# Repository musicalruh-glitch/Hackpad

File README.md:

### **Hackpad**

This hackpad is an extension of my regular keyboard! It makes it easier to game and change audio. The Hackpad is Bluetooth, so it'll connect to the PC. Unfortuneately.. I FORGOT TO ADD SOMETHING UNDERTALE RELATED GRAHHHH so the plan is when I get my CAD, I'll paint an undertale heart on the case or something
:DDD that's basically all there is to it lol, originally it was only 3 keys but I wanted to end off the design weeks with a bang, so here it is!! An extension of the keyboard, if all the arrow keys are separated, that makes it infinitely easier to game and stuff, volume buttons too because why not. Oh and the OLED screen because why not heheh. 

___

——

## **Here’s what each button does!**
Switches:
1. SW1: Same function as up arrow key on keyboard
2. SW2: Same function as down arrow key on keyboard
3. SW3: Same function as left arrow key on keyboard
4. SW4: Same function as right arrow key on keyboard
5. SW5: Same function as volume up key on keyboard
6. SW6: Same function as volume down key on keyboard
7. SW7: Same function as mute key on keyboard

There's also an OLED screen, it'll display whether the Hackpad is connected or not! It's findable as "Hackpad" when you turn bluetooth on. Seems a bit generic lol, I may want to change that.

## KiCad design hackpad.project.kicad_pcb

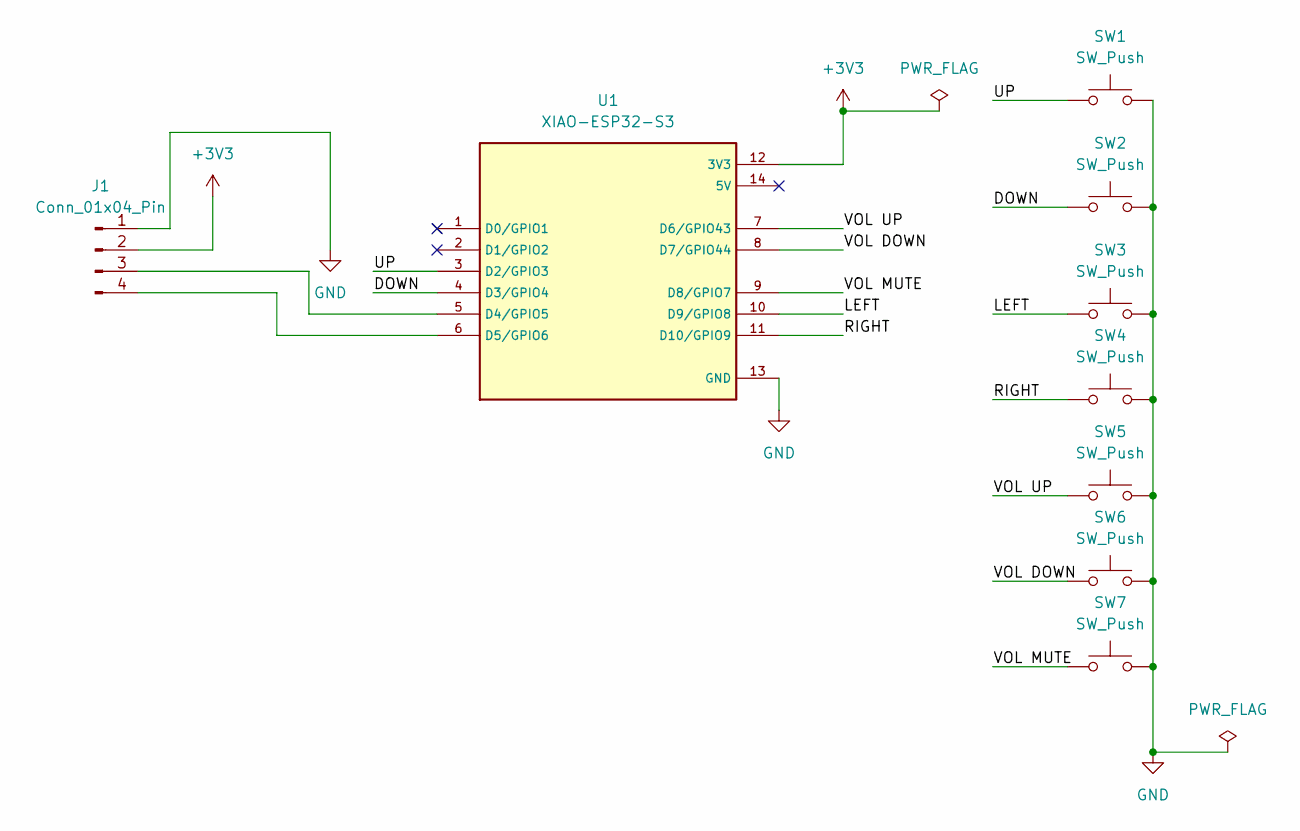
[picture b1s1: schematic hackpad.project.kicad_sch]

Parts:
J1: Conn_01x04_Pin; PinHeader_1x04_P2.54mm_Vertical
SW1, SW2, SW3, SW4, SW5, SW6, SW7: SW_Push; SW_Cherry_MX_1.00u_PCB
U1: XIAO-ESP32-S3; XIAO ESP32-S3; PARTREV April 22nd, 2026

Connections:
+3V3: J1.2, U1.12 (3V3)
/DOWN: SW2.1, U1.4 (D3/GPIO4)
/LEFT: SW3.1, U1.10 (D9/GPIO8)
/RIGHT: SW4.1, U1.11 (D10/GPIO9)
/UP: SW1.1, U1.3 (D2/GPIO3)
/VOL DOWN: SW6.1, U1.8 (D7/GPIO44)
/VOL MUTE: SW7.1, U1.9 (D8/GPIO7)
/VOL UP: SW5.1, U1.7 (D6/GPIO43)
GND: J1.1, SW1.2, SW2.2, SW3.2, SW4.2, SW5.2, SW6.2, SW7.2, U1.13 (GND)
unnamed: J1.3, U1.5 (D4/GPIO5)
unnamed: J1.4, U1.6 (D5/GPIO6)

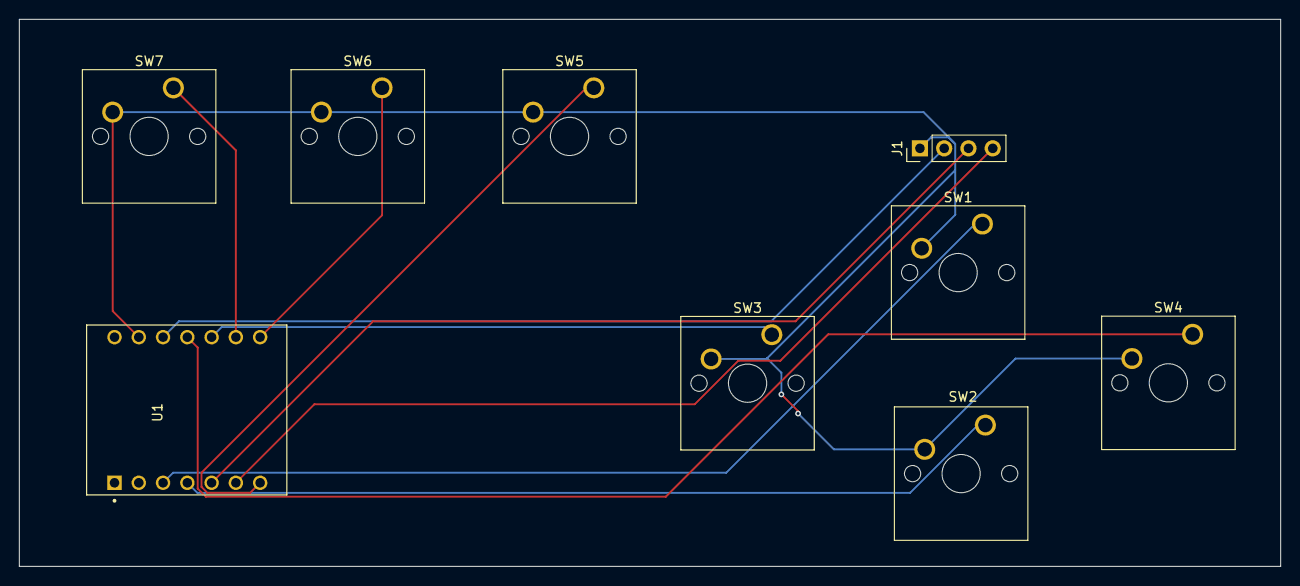
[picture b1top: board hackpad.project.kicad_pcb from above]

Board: 2 copper layers, 132.0 x 57.2 mm, 9 parts (0 on the bottom side), 11 nets.

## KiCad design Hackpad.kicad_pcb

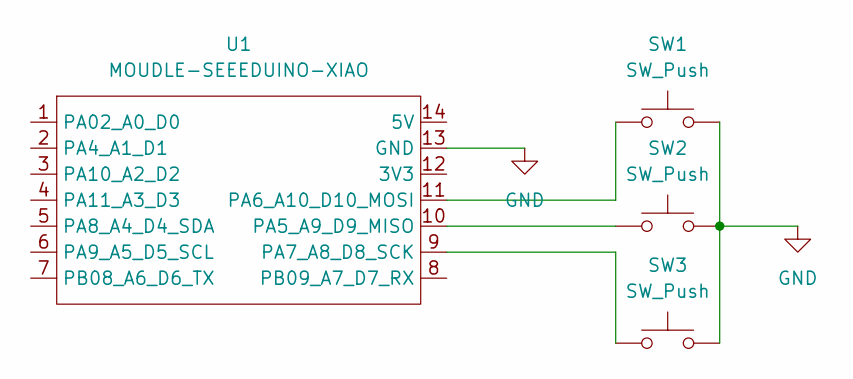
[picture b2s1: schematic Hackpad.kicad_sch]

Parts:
SW1, SW2, SW3: SW_Push; SW_Cherry_MX_1.00u_PCB
U1: MOUDLE-SEEEDUINO-XIAO; XIAO-Generic-Hybrid-14P-2.54-21X17.8MM

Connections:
GND: SW1.2, SW2.2, SW3.2, U1.13 (GND)
unnamed: SW2.1, U1.10 (PA5_A9_D9_MISO)
unnamed: SW1.1, U1.11 (PA6_A10_D10_MOSI)
unnamed: SW3.1, U1.9 (PA7_A8_D8_SCK)

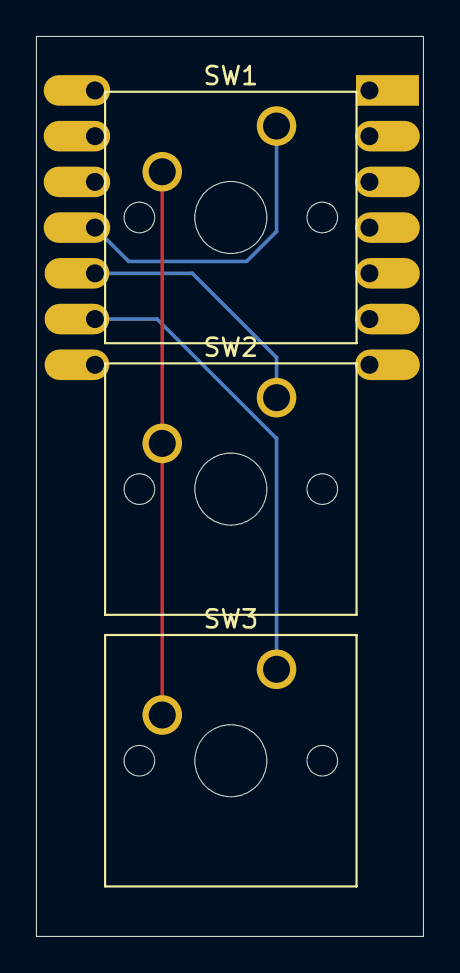
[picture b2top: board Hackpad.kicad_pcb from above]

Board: 2 copper layers, 21.5 x 50.0 mm, 4 parts (1 on the bottom side), 4 nets.
